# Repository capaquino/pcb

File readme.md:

Personal PCB projects portfolio

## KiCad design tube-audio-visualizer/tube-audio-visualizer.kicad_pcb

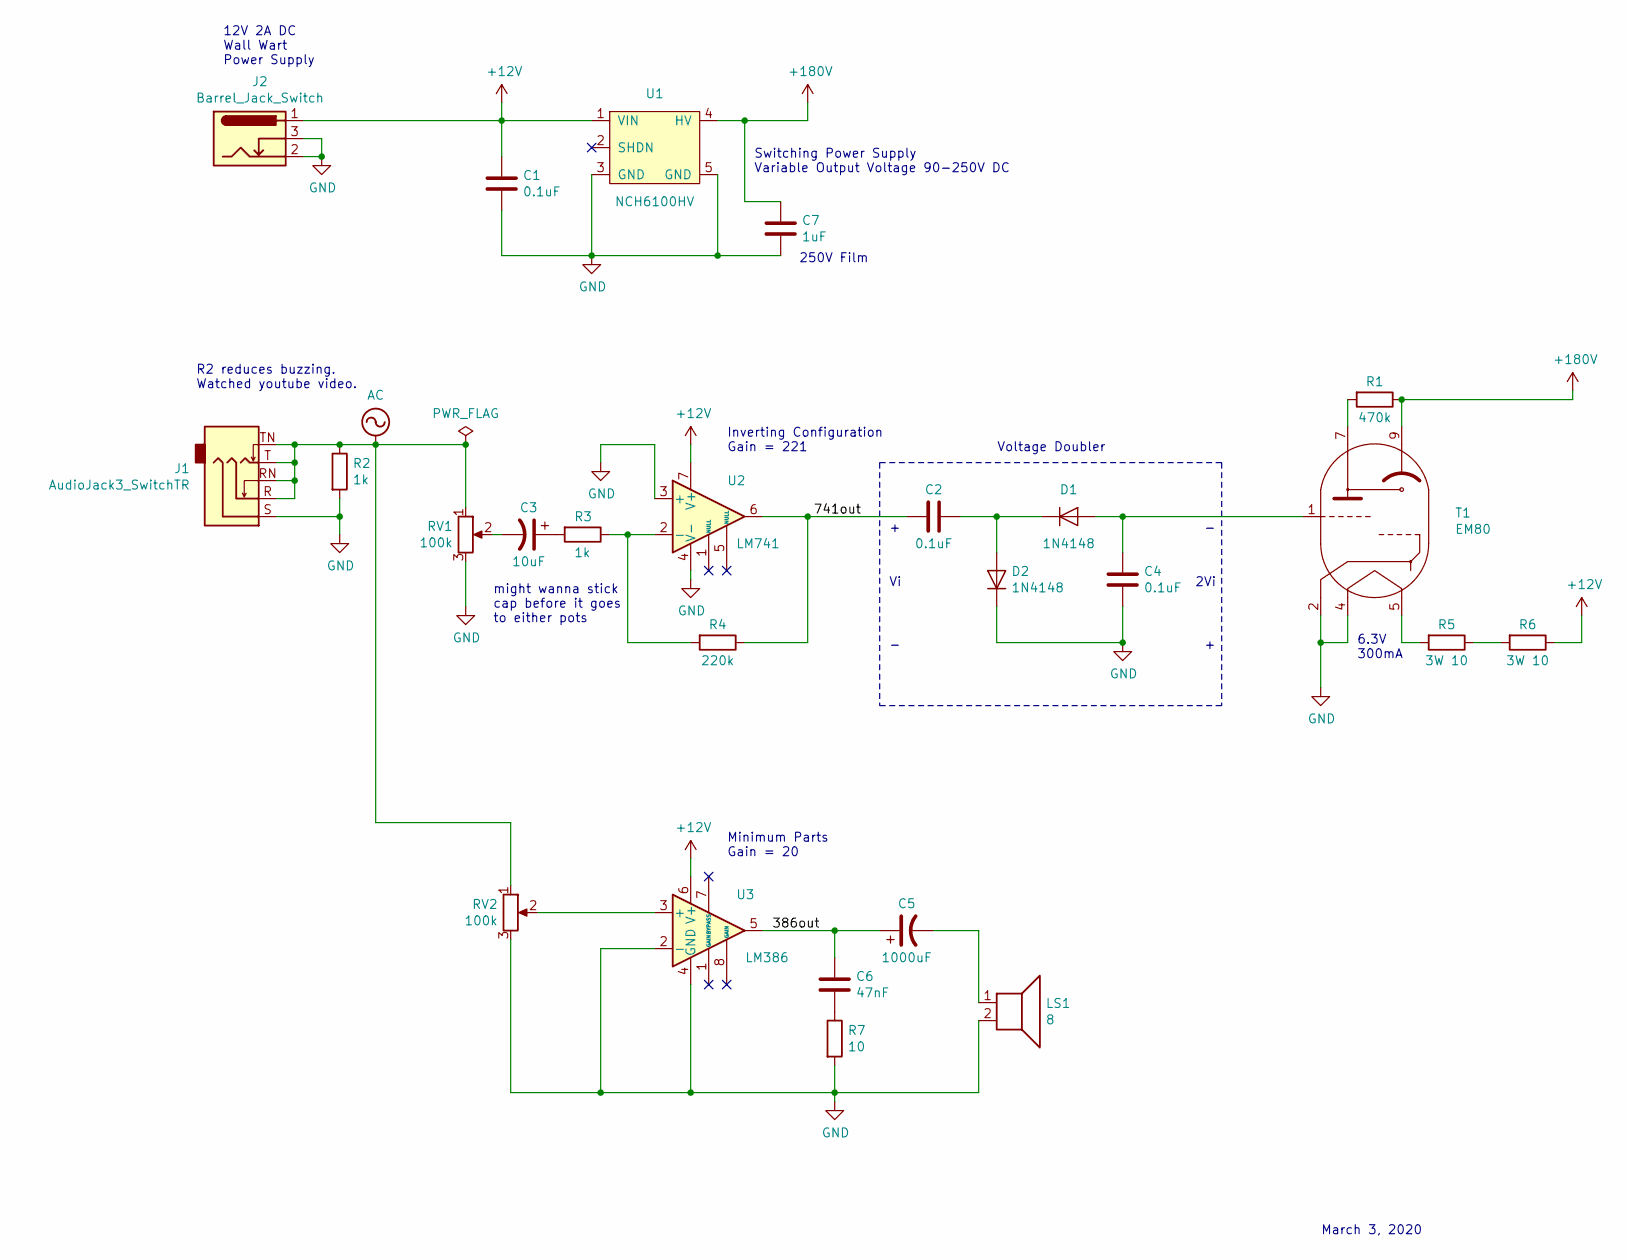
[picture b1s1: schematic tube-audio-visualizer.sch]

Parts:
C1, C2, C4: 0.1uF; C_Disc_D5.0mm_W2.5mm_P5.00mm
C3: 10uF; CP_Radial_D5.0mm_P2.00mm
C5: 1000uF; CP_Radial_D8.0mm_P3.50mm
C6: 47nF; C_Disc_D3.0mm_W2.0mm_P2.50mm
C7: 1uF; Cap_Film_250V_1uF_Nichicon
D1, D2: 1N4148; D_DO-35_SOD27_P7.62mm_Horizontal
J1: AudioJack3_SwitchTR; AudioJack_3_5_mm_Female
J2: Barrel_Jack_Switch; BarrelJack_CUI_PJ-102AH_Horizontal
LS1: 8; PinSocket_1x02_P2.54mm_Vertical
R1: 470k; R_Axial_DIN0207_L6.3mm_D2.5mm_P10.16mm_Horizontal
R2, R3: 1k; R_Axial_DIN0207_L6.3mm_D2.5mm_P10.16mm_Horizontal
R4: 220k; R_Axial_DIN0207_L6.3mm_D2.5mm_P10.16mm_Horizontal
R5, R6: 3W 10; R_Axial_DIN0516_L15.5mm_D5.0mm_P20.32mm_Horizontal
R7: 10; R_Axial_DIN0207_L6.3mm_D2.5mm_P10.16mm_Horizontal
RV1, RV2: 100k; Potentiometer_Bourns_3386P_Vertical
T1: EM80; Noval_B9A_Ceramic
U1: NCH6100HV; NCH6100HV_PinSockets
U2: LM741; DIP-8_W7.62mm
U3: LM386; DIP-8_W7.62mm

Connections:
+12V: C1.1, J2.1, R6.1, U1.1 (VIN), U2.7 (V+), U3.6 (V+)
+180V: C7.1, R1.1, T1.9 (display), U1.4 (HV)
/386out: C5.1, C6.1, U3.5
/741out: C2.2, R4.1, U2.6
AC: J1.R, J1.RN, J1.T, J1.TN, R2.1, RV1.1, RV2.1
GND: C1.2, C4.2, C7.2, D2.1 (K), J1.S, J2.2, J2.3, LS1.2, R2.2, R7.2, RV1.3, RV2.3, T1.2 (cathode), T1.4 (f1), U1.3 (GND), U1.5 (GND), U2.3 (+), U2.4 (V-), U3.2 (-), U3.4 (GND)
unnamed: C2.1, D1.1 (K), D2.2 (A)
unnamed: C3.1, R3.2
unnamed: C3.2, RV1.2
unnamed: C4.1, D1.2 (A), T1.1 (grid)
unnamed: C5.2, LS1.1
unnamed: C6.2, R7.1
unnamed: R1.2, T1.7 (plate)
unnamed: R3.1, R4.2, U2.2 (-)
unnamed: R5.1, R6.2
unnamed: R5.2, T1.5 (f2)
unnamed: RV2.2, U3.3 (+)

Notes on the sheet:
Voltage Doubler
2Vi
March 3, 2020
6.3V 300mA
Minimum Parts Gain = 20
Inverting Configuration Gain = 221
Switching Power Supply Variable Output Voltage 90-250V DC
might wanna stick cap before it goes to either pots
12V 2A DC Wall Wart Power Supply
R2 reduces buzzing. Watched youtube video.
250V Film

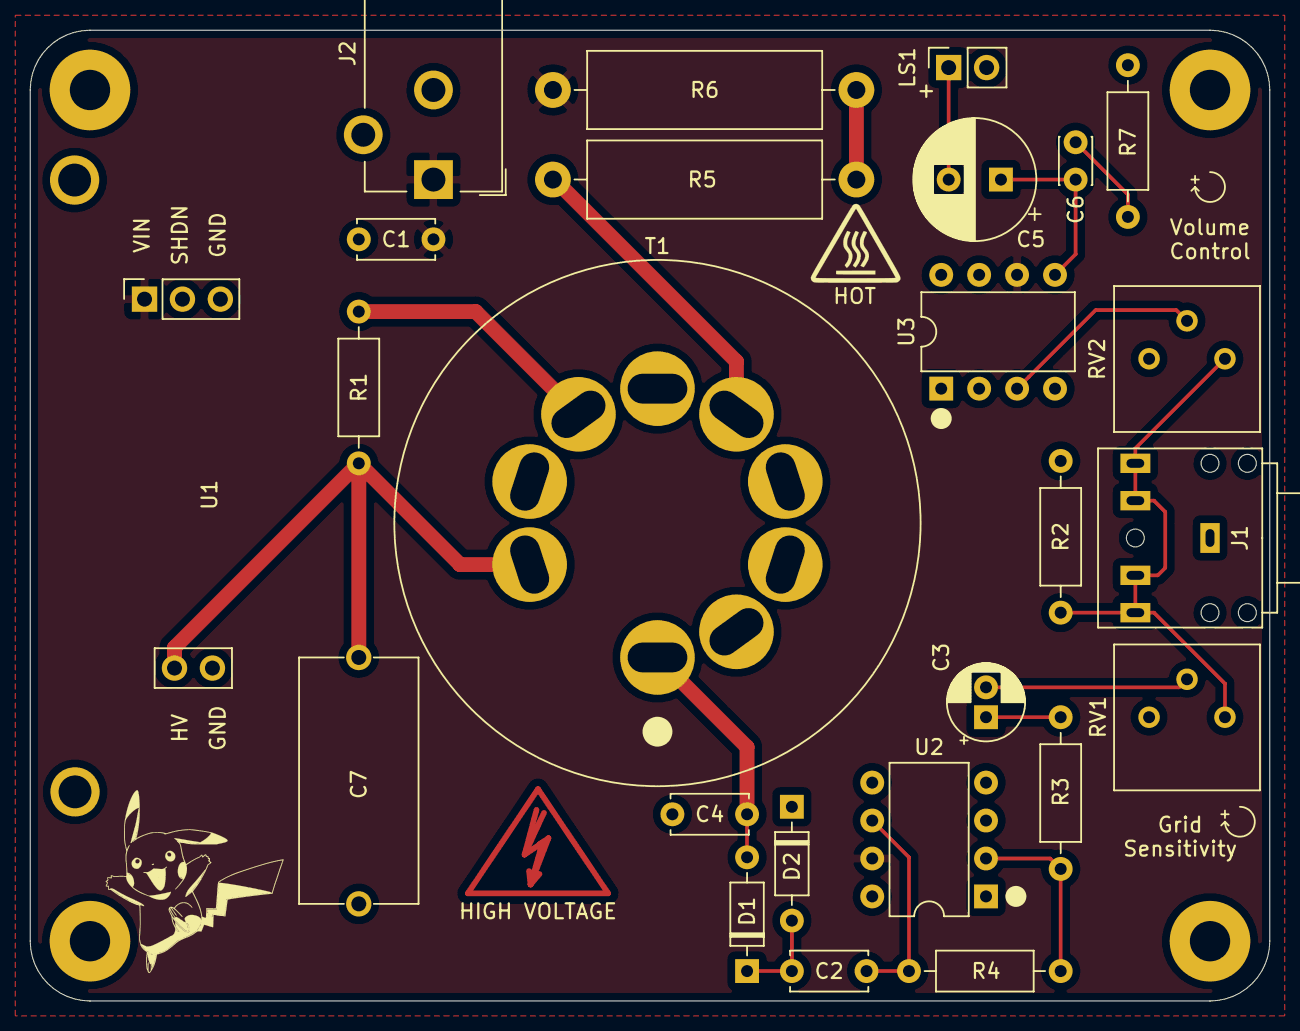
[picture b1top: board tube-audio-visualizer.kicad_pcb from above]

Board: 2 copper layers, 83.0 x 65.0 mm, 25 parts (0 on the bottom side), 17 nets.

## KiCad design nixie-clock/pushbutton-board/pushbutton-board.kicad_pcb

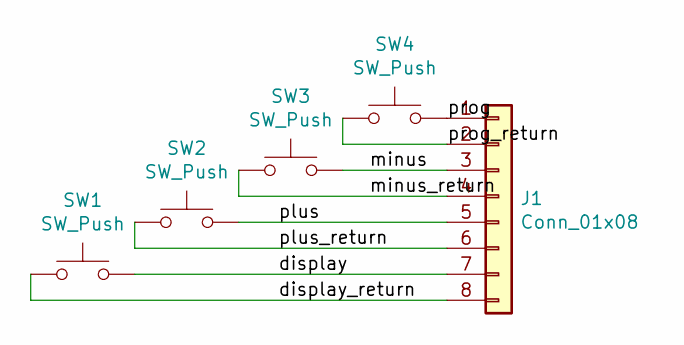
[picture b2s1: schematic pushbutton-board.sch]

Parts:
J1: Conn_01x08; PinHeader_2x04_P2.54mm_Vertical
SW1, SW2, SW3, SW4: SW_Push; SW_PUSH_6mm

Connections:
/display: J1.7, SW1.2
/display_return: J1.8, SW1.1
/minus: J1.3, SW3.2
/minus_return: J1.4, SW3.1
/plus: J1.5, SW2.2
/plus_return: J1.6, SW2.1
/prog: J1.1, SW4.2
/prog_return: J1.2, SW4.1

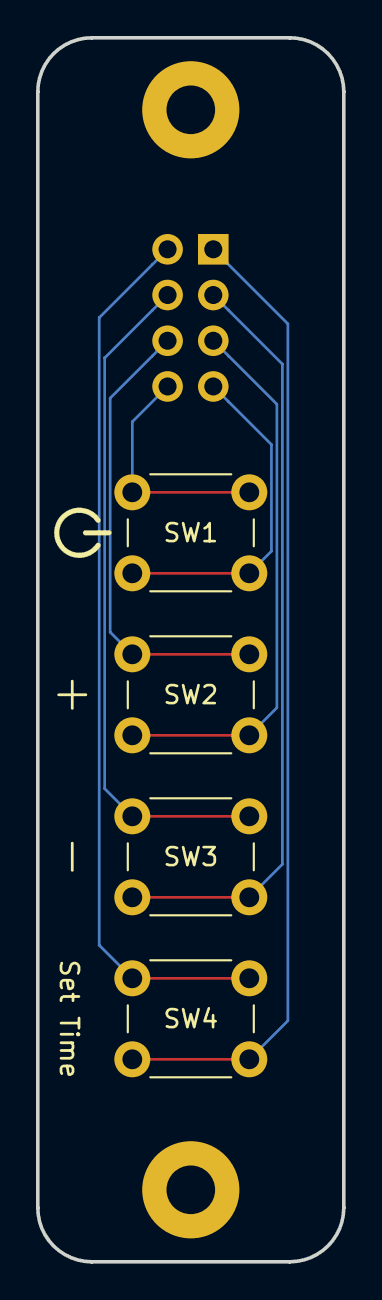
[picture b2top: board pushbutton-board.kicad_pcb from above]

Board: 2 copper layers, 17.0 x 68.0 mm, 5 parts (1 on the bottom side), 8 nets.

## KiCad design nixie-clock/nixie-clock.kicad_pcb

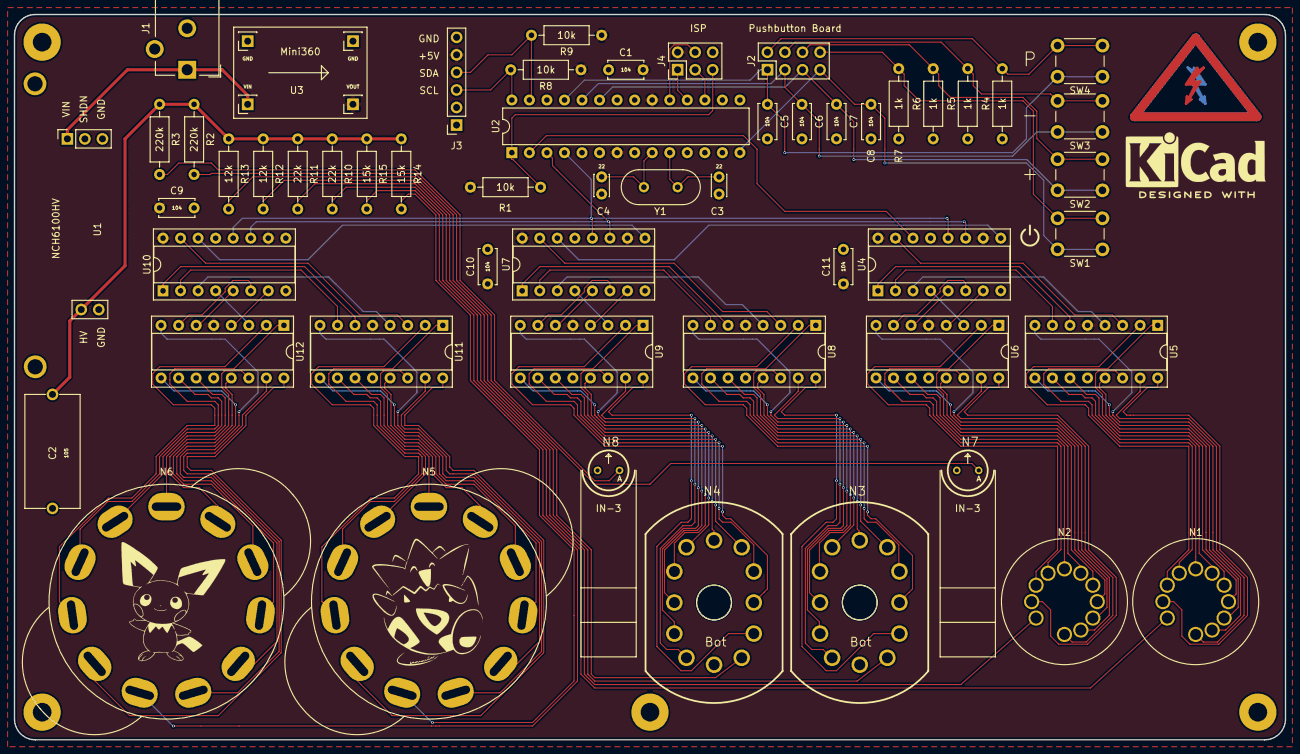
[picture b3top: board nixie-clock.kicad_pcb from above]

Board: 2 copper layers, 184.0 x 105.0 mm, 55 parts (0 on the bottom side), 117 nets.

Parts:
C1, C5, C6, C7, C8, C9, C10, C11: 0.1uF; C_Disc_D5.0mm_W2.5mm_P5.00mm
C2: 1uF; Cap_Film_250V_1uF_Nichicon
C3, C4: 22pF; C_Disc_D3.0mm_W2.0mm_P2.50mm
J1: Barrel_Jack_Switch; BarrelJack_CUI_PJ-102AH_Horizontal
J2: Conn_01x08; PinHeader_2x04_P2.54mm_Vertical
J3: Conn_01x06; PinSocket_1x06_P2.54mm_Vertical
J4: AVR-ISP-6; PinHeader_2x03_P2.54mm_Vertical
N1, N2: IN-2; IN-2_Socket_Pins
N3, N4: IN-12A; nixies-us-IN-12-DSUB
N5, N6: IN-1; IN-1_Socket
N7, N8: IN-3; IN-3_Bare
R1, R8, R9: 10k; R_Axial_DIN0207_L6.3mm_D2.5mm_P10.16mm_Horizontal
R2, R3: 220k; R_Axial_DIN0207_L6.3mm_D2.5mm_P10.16mm_Horizontal
R4, R5, R6, R7: 1k; R_Axial_DIN0207_L6.3mm_D2.5mm_P10.16mm_Horizontal
R10, R11: 22k; R_Axial_DIN0207_L6.3mm_D2.5mm_P10.16mm_Horizontal
R12, R13: 12k; R_Axial_DIN0207_L6.3mm_D2.5mm_P10.16mm_Horizontal
R14, R15: 15k; R_Axial_DIN0207_L6.3mm_D2.5mm_P10.16mm_Horizontal
SW1, SW2, SW3, SW4: SW_Push; SW_PUSH_6mm
U1: NCH6100HV; NCH6100HV_PinSockets
U2: ATmega328P-PU; DIP-28_W7.62mm
U3: Mini360_Buck; Mini360_PinSockets
U4, U7, U10: 74HC595; DIP-16_W7.62mm_Socket
U5, U6, U8, U9, U11, U12: 74141; DIP-16_W7.62mm_Socket
Y1: 8MHz; Crystal_HC49-4H_Vertical

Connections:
+5V: C1.1, C9.1, C10.1, C11.1, J3.5, J4.2, R1.1, R8.1, R9.1, U2.7, U2.20, U3.3, U4.10, U4.16, U5.5, U6.5, U7.10, U7.16, U8.5, U9.5, U10.10, U10.16, U11.5, U12.5
+12V: J1.1, U1.1, U3.1
+170V: C2.1, R2.1, R3.1, R10.1, R11.1, R12.1, R13.1, R14.1, R15.1, U1.4
/AnodeN7: N7.A, R2.2
/AnodeN8: N8.A, R3.2
/shiftout/AnodeN1: N1.A, R10.2
/shiftout/AnodeN2: N2.A, R11.2
/shiftout/AnodeN3: N3.A, R12.2
/shiftout/AnodeN4: N4.A, R13.2
/shiftout/AnodeN5: N5.A, R14.2
/shiftout/AnodeN6: N6.A, R15.2
/shiftout/N1_0: N1.0, U5.16
/shiftout/N1_1: N1.1, U5.15
/shiftout/N1_2: N1.2, U5.8
/shiftout/N1_3: N1.3, U5.9
/shiftout/N1_4: N1.4, U5.13
/shiftout/N1_5: N1.5, U5.14
/shiftout/N1_6: N1.6, U5.11
/shiftout/N1_7: N1.7, U5.10
/shiftout/N1_8: N1.8, U5.1
/shiftout/N1_9: N1.9, U5.2
/shiftout/N1_A: U4.15, U5.3
/shiftout/N1_B: U4.1, U5.6
/shiftout/N1_C: U4.2, U5.7
/shiftout/N1_D: U4.3, U5.4
/shiftout/N2_0: N2.0, U6.16
/shiftout/N2_1: N2.1, U6.15
/shiftout/N2_2: N2.2, U6.8
/shiftout/N2_3: N2.3, U6.9
/shiftout/N2_4: N2.4, U6.13
/shiftout/N2_5: N2.5, U6.14
/shiftout/N2_6: N2.6, U6.11
/shiftout/N2_7: N2.7, U6.10
/shiftout/N2_8: N2.8, U6.1
/shiftout/N2_9: N2.9, U6.2
/shiftout/N2_A: U4.4, U6.3
/shiftout/N2_B: U4.5, U6.6
/shiftout/N2_C: U4.6, U6.7
/shiftout/N2_D: U4.7, U6.4
/shiftout/N3_0: N3.0, U8.16
/shiftout/N3_1: N3.1, U8.15
/shiftout/N3_2: N3.2, U8.8
/shiftout/N3_3: N3.3, U8.9
/shiftout/N3_4: N3.4, U8.13
/shiftout/N3_5: N3.5, U8.14
/shiftout/N3_6: N3.6, U8.11
/shiftout/N3_7: N3.7, U8.10
/shiftout/N3_8: N3.8, U8.1
/shiftout/N3_9: N3.9, U8.2
/shiftout/N3_A: U7.15, U8.3
/shiftout/N3_B: U7.1, U8.6
/shiftout/N3_C: U7.2, U8.7
/shiftout/N3_D: U7.3, U8.4
/shiftout/N4_0: N4.0, U9.16
/shiftout/N4_1: N4.1, U9.15
/shiftout/N4_2: N4.2, U9.8
/shiftout/N4_3: N4.3, U9.9
/shiftout/N4_4: N4.4, U9.13
/shiftout/N4_5: N4.5, U9.14
/shiftout/N4_6: N4.6, U9.11
/shiftout/N4_7: N4.7, U9.10
/shiftout/N4_8: N4.8, U9.1
/shiftout/N4_9: N4.9, U9.2
/shiftout/N4_A: U7.4, U9.3
/shiftout/N4_B: U7.5, U9.6
/shiftout/N4_C: U7.6, U9.7
/shiftout/N4_D: U7.7, U9.4
/shiftout/N5_0: N5.0, U11.16
/shiftout/N5_1: N5.1, U11.15
/shiftout/N5_2: N5.2, U11.8
/shiftout/N5_3: N5.3, U11.9
/shiftout/N5_4: N5.4, U11.13
/shiftout/N5_5: N5.5, U11.14
/shiftout/N5_6: N5.6, U11.11
/shiftout/N5_7: N5.7, U11.10
/shiftout/N5_8: N5.8, U11.1
/shiftout/N5_9: N5.9, U11.2
/shiftout/N5_A: U10.15, U11.3
/shiftout/N5_B: U10.1, U11.6
/shiftout/N5_C: U10.2, U11.7
/shiftout/N5_D: U10.3, U11.4
/shiftout/N6_0: N6.0, U12.16
/shiftout/N6_1: N6.1, U12.15
/shiftout/N6_2: N6.2, U12.8
/shiftout/N6_3: N6.3, U12.9
/shiftout/N6_4: N6.4, U12.13
/shiftout/N6_5: N6.5, U12.14
/shiftout/N6_6: N6.6, U12.11
/shiftout/N6_7: N6.7, U12.10
/shiftout/N6_8: N6.8, U12.1
/shiftout/N6_9: N6.9, U12.2
/shiftout/N6_A: U10.4, U12.3
/shiftout/N6_B: U10.5, U12.6
/shiftout/N6_C: U10.6, U12.7
/shiftout/N6_D: U10.7, U12.4
GND: C1.2, C2.2, C3.2, C4.2, C5.2, C6.2, C7.2, C8.2, C9.2, C10.2, C11.2, J1.2, J1.3, J3.6, J4.6, N7.K, N8.K, R4.1, R5.1, R6.1, R7.1, U1.3, U1.5, U2.8, U2.22, U3.2, U3.4, U4.8, U4.13, U5.12, U6.12, U7.8, U7.13, U8.12, U9.12, U10.8, U10.13, U11.12, U12.12
unnamed: J2.2, R4.2, SW4.2
unnamed: J2.4, R5.2, SW3.2
unnamed: J2.6, R6.2, SW2.2
unnamed: J2.8, R7.2, SW1.2
unnamed: U4.9, U7.14
unnamed: U7.9, U10.14
SCL: J3.3, R8.2, U2.28
SDA: J3.4, R9.2, U2.27
SPI_MISO: J4.1, U2.18
SPI_MOSI: J4.4, U2.19
SPI_RST: J4.5, R1.2, U2.1
SPI_SCK: J4.3, U2.17
SRCLK: U2.3, U4.11, U7.11, U10.11
SRDATA: U2.2, U4.14
SRLATCH: U2.4, U4.12, U7.12, U10.12
XTAL1: C3.1, U2.10, Y1.1
XTAL2: C4.1, U2.9, Y1.2
pb_display_on: C8.1, J2.7, SW1.1, U2.14
pb_minus: C6.1, J2.3, SW3.1, U2.24
pb_plus: C7.1, J2.5, SW2.1, U2.23
pb_programming_select: C5.1, J2.1, SW4.1, U2.25

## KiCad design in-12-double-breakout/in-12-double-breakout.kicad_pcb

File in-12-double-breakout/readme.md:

IN12 breakout board kicad project.

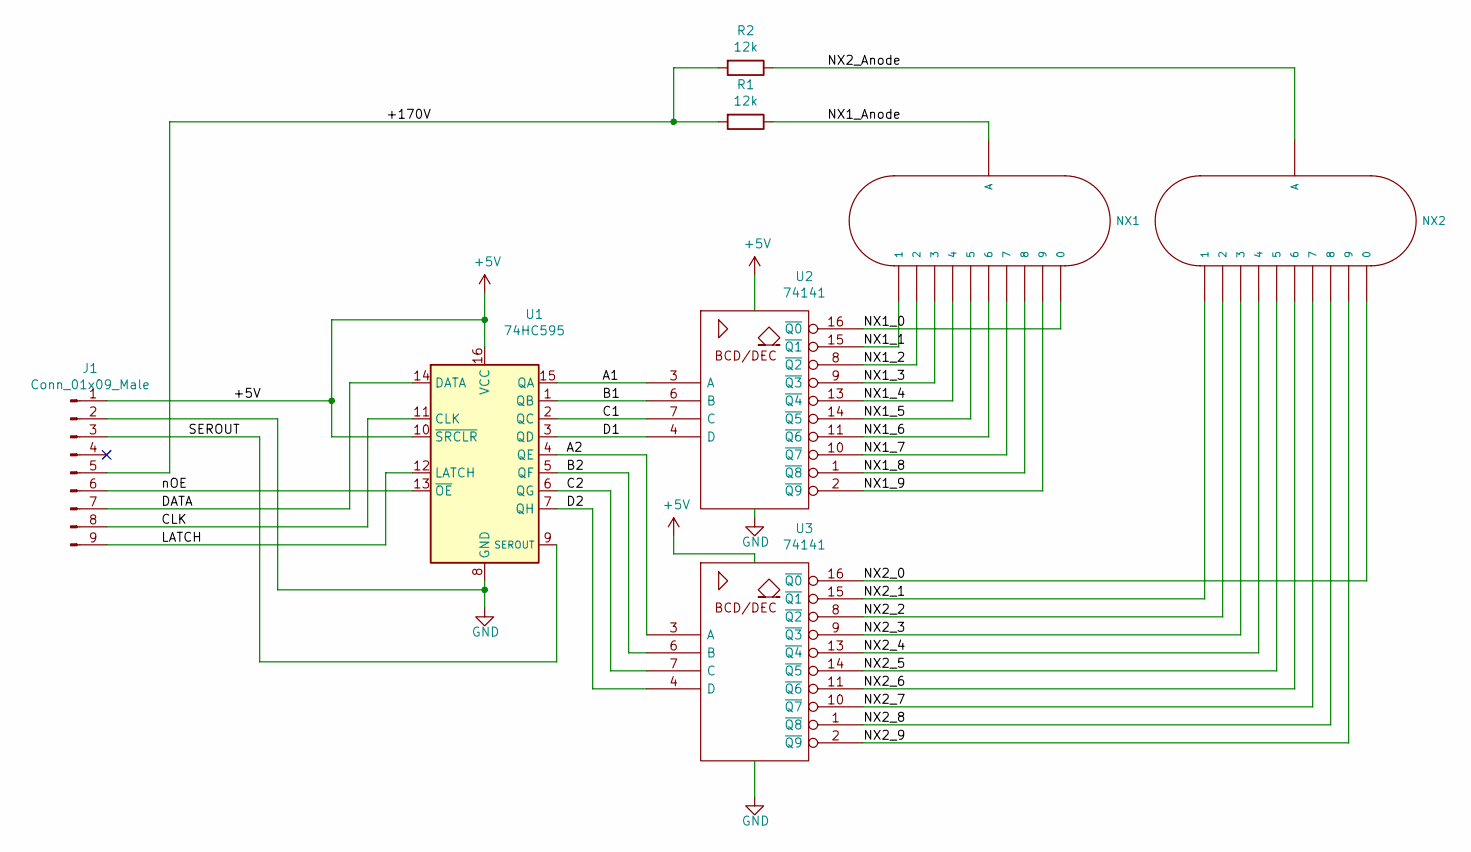
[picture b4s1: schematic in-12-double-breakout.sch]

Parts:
J1: Conn_01x09_Male; PinHeader_1x09_P2.54mm_Horizontal
NX1, NX2: IN-12A; nixies-us_IN-12
R1, R2: 12k; R_Axial_DIN0207_L6.3mm_D2.5mm_P10.16mm_Horizontal
U1: 74HC595; DIP-16_W7.62mm_Socket
U2, U3: 74141; DIP-16_W7.62mm_Socket

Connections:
+5V: J1.1, U1.10 (~SRCLR), U1.16 (VCC), U2.5 (VCC), U3.5 (VCC)
/+170V: J1.5, R1.2, R2.2
/A1: U1.15 (QA), U2.3 (A)
/A2: U1.4 (QE), U3.3 (A)
/B1: U1.1 (QB), U2.6 (B)
/B2: U1.5 (QF), U3.6 (B)
/C1: U1.2 (QC), U2.7 (C)
/C2: U1.6 (QG), U3.7 (C)
/CLK: J1.8, U1.11 (CLK)
/D1: U1.3 (QD), U2.4 (D)
/D2: U1.7 (QH), U3.4 (D)
/DATA: J1.7, U1.14 (DATA)
/LATCH: J1.9, U1.12 (LATCH)
/NX1_0: NX1.0, U2.16 (~Q0)
/NX1_1: NX1.1, U2.15 (~Q1)
/NX1_2: NX1.2, U2.8 (~Q2)
/NX1_3: NX1.3, U2.9 (~Q3)
/NX1_4: NX1.4, U2.13 (~Q4)
/NX1_5: NX1.5, U2.14 (~Q5)
/NX1_6: NX1.6, U2.11 (~Q6)
/NX1_7: NX1.7, U2.10 (~Q7)
/NX1_8: NX1.8, U2.1 (~Q8)
/NX1_9: NX1.9, U2.2 (~Q9)
/NX1_Anode: NX1.A, R1.1
/NX2_0: NX2.0, U3.16 (~Q0)
/NX2_1: NX2.1, U3.15 (~Q1)
/NX2_2: NX2.2, U3.8 (~Q2)
/NX2_3: NX2.3, U3.9 (~Q3)
/NX2_4: NX2.4, U3.13 (~Q4)
/NX2_5: NX2.5, U3.14 (~Q5)
/NX2_6: NX2.6, U3.11 (~Q6)
/NX2_7: NX2.7, U3.10 (~Q7)
/NX2_8: NX2.8, U3.1 (~Q8)
/NX2_9: NX2.9, U3.2 (~Q9)
/NX2_Anode: NX2.A, R2.1
/SEROUT: J1.3, U1.9 (SEROUT)
/nOE: J1.6, U1.13 (~OE)
GND: J1.2, U1.8 (GND), U2.12 (GND), U3.12 (GND)

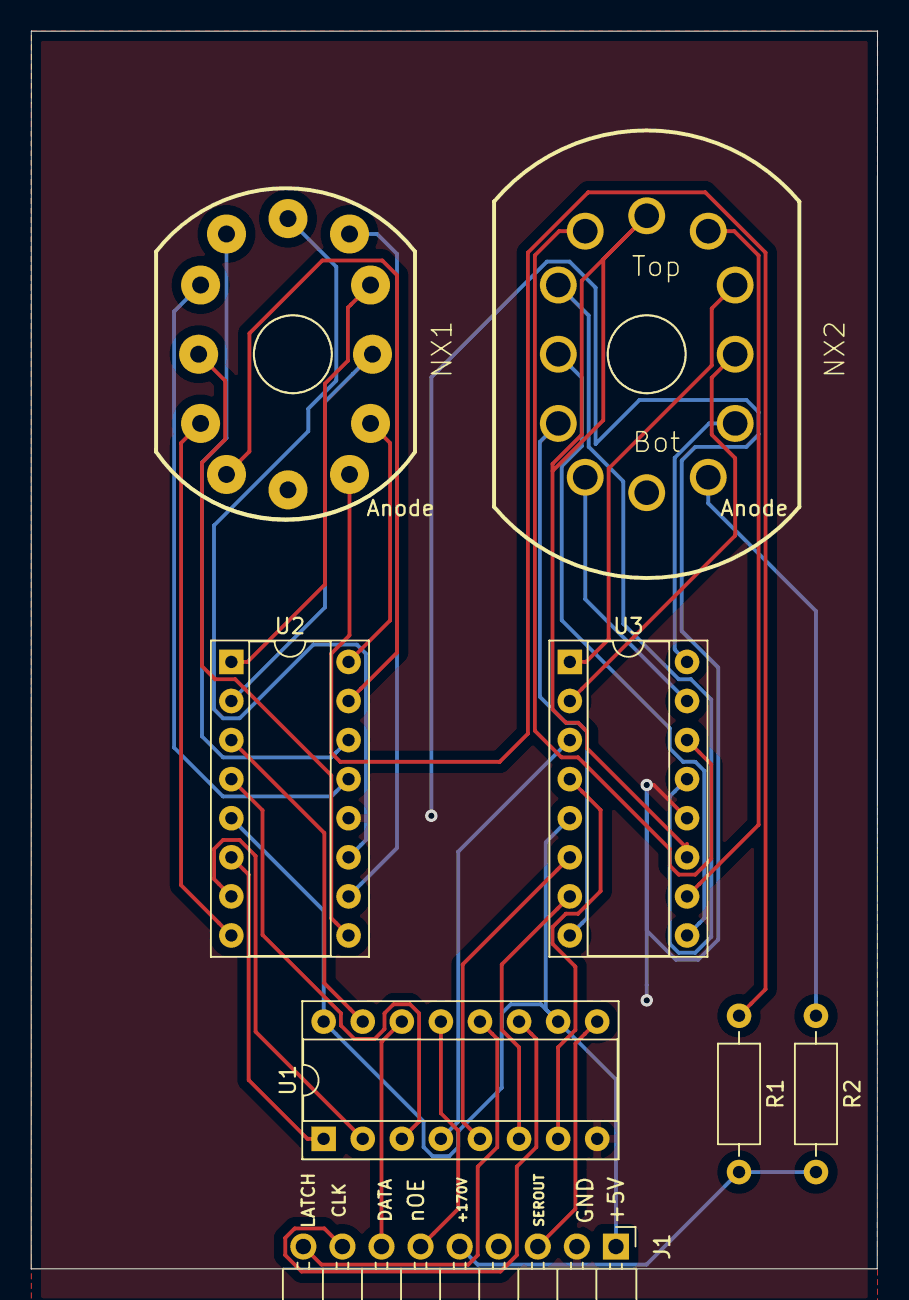
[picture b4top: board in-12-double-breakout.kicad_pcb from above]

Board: 2 copper layers, 55.0 x 80.5 mm, 8 parts (0 on the bottom side), 38 nets.

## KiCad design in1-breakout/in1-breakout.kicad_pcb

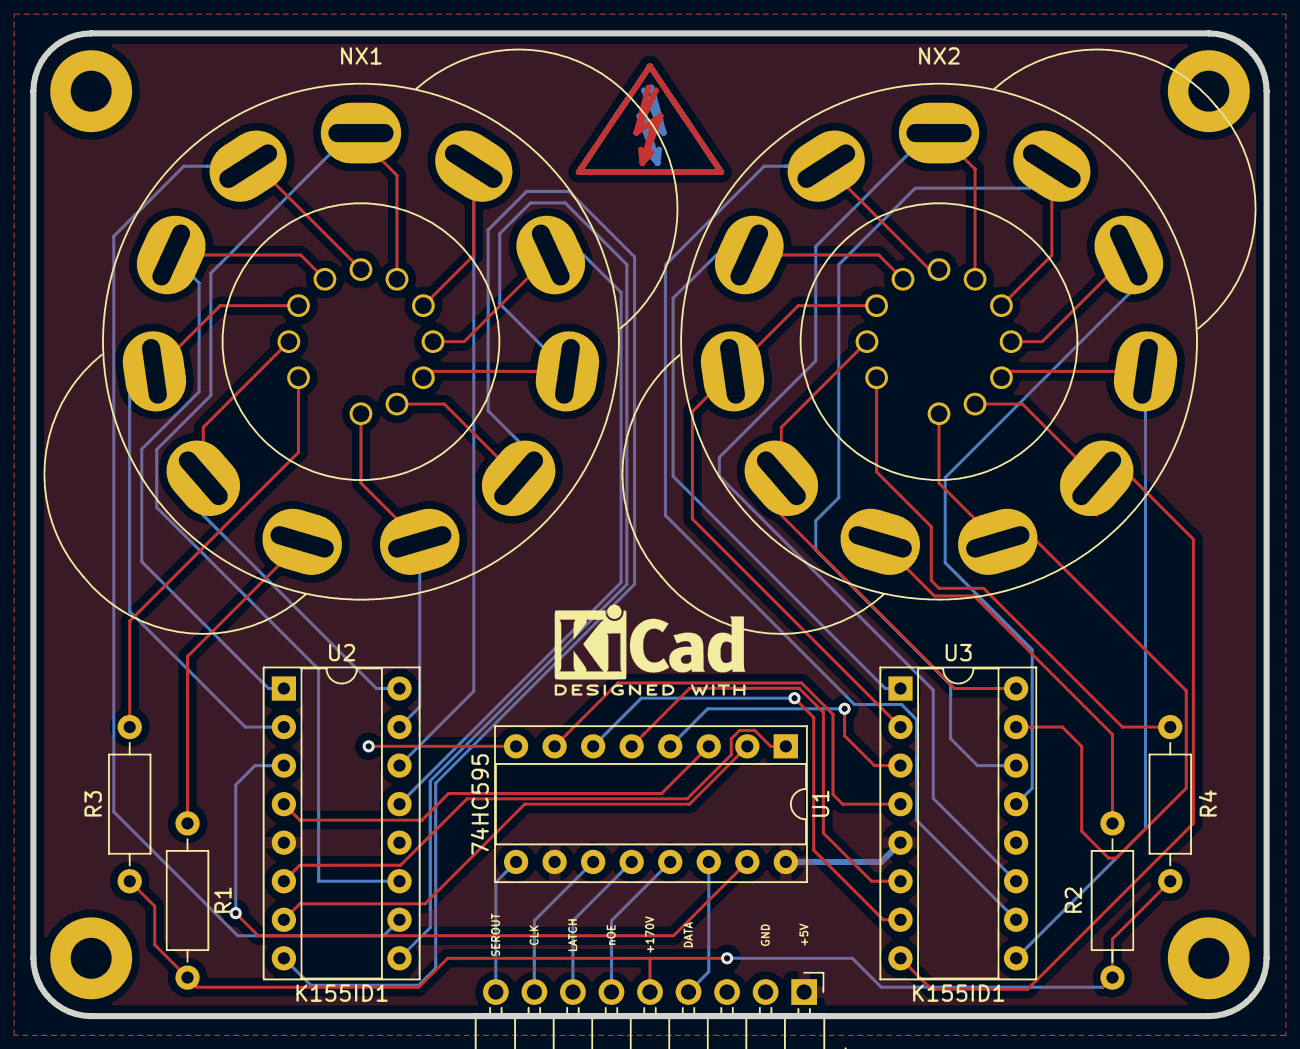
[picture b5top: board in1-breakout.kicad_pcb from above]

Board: 2 copper layers, 81.3 x 64.8 mm, 12 parts (0 on the bottom side), 40 nets.

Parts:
J1: Conn_01x09_Male; PinHeader_1x09_P2.54mm_Horizontal
NX1, NX2: IN-1; IN-1_Socket
NX3, NX4: IN-2; IN-2_Bare
R1, R2: 15k; R_Axial_DIN0207_L6.3mm_D2.5mm_P10.16mm_Horizontal
R3, R4: 22k; R_Axial_DIN0207_L6.3mm_D2.5mm_P10.16mm_Horizontal
U1: 74HC595; DIP-16_W7.62mm_Socket
U2, U3: K155ID1; DIP-16_W7.62mm_Socket

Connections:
+5V: J1.1, U1.10, U1.16, U2.5, U3.5
/+170V: J1.5, R1.2, R2.2, R3.1, R4.1
/A1: U1.15, U2.3
/A2: U1.4, U3.3
/B1: U1.1, U2.6
/B2: U1.5, U3.6
/C1: U1.2, U2.7
/C2: U1.6, U3.7
/CLK: J1.8, U1.11
/D1: U1.3, U2.4
/D2: U1.7, U3.4
/DATA: J1.4, U1.14
/LATCH: J1.7, U1.12
/NX1_0: NX1.0, NX3.0, U2.16
/NX1_1: NX1.1, NX3.1, U2.15
/NX1_2: NX1.2, NX3.2, U2.8
/NX1_3: NX1.3, NX3.3, U2.9
/NX1_4: NX1.4, NX3.4, U2.13
/NX1_5: NX1.5, NX3.5, U2.14
/NX1_6: NX1.6, NX3.6, U2.11
/NX1_7: NX1.7, NX3.7, U2.10
/NX1_8: NX1.8, NX3.8, U2.1
/NX1_9: NX1.9, NX3.9, U2.2
/NX1_Anode: NX1.A, R1.1
/NX2_0: NX2.0, NX4.0, U3.16
/NX2_1: NX2.1, NX4.1, U3.15
/NX2_2: NX2.2, NX4.2, U3.8
/NX2_3: NX2.3, NX4.3, U3.9
/NX2_4: NX2.4, NX4.4, U3.13
/NX2_5: NX2.5, NX4.5, U3.14
/NX2_6: NX2.6, NX4.6, U3.11
/NX2_7: NX2.7, NX4.7, U3.10
/NX2_8: NX2.8, NX4.8, U3.1
/NX2_9: NX2.9, NX4.9, U3.2
/NX2_Anode: NX2.A, R2.1
/NX3_Anode: NX3.A, R3.2
/NX4_Anode: NX4.A, R4.2
/SEROUT: J1.9, U1.9
/nOE: J1.6, U1.13
GND: J1.2, U1.8, U2.12, U3.12

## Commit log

2020-03-03 Initial commit. Has in1/in2 combined breakout board.
2020-03-04 Migrated all previous pcb projects to this repository.
2020-03-30 Added IN-2 footprint for socket pins.
2020-03-31 Added IN-2_Socket_Pins_test project for testing IN-2 footprint that uses eBay socket pins.
2020-03-31 Added nixie-clock project. Added symbols to schematic.
2020-04-06 Worked on schematic. Added child sheet. See TODO at left of root. Created Mini360 symbol.
2020-04-19 Added footprint for NCH6100HV switching power supply.
2020-04-22 Added footprints for mini360 buck and nichicon 1uf 250v film cap. Updated nixie-clock schematic with values. Starting to update schematic with daisy-chained configuration now that I figured out the p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
2020-04-23 Finished schematic for nixie clock main board. Added IN-3 footprint.
2020-04-23 Began nixie-clock pcb.
2020-04-23 Placed parts on board in approximate final locations. Created trace breakout for nixie tubes.
2020-04-24 Readded pushbuttons to mainboard as an option. Beginning K155ID1-nixie exchange zone.
2020-04-24 Both sides of exchange zone ready for connecting for IN-1, IN-2. Discovered IN-12 has reverse order so will need to redo traces for the K155ID1s attached to those nixies.
2020-04-24 Finished K155ID1-nixie exchange zone routing.
2020-04-24 Routed near microcontroller. Going to finish 74HC595-K155ID1 routing before returning to micro area.
2020-04-24 Finished seconds and minutes SR-K155ID1 exchange. Hours one is a bit different. Rotated SRs for better pin placement.
2020-04-24 About to begin inter-74HC595 signals. Save point.
2020-04-24 Finished inter-74HC595 routing.
2020-04-24 Fixed anode net names. Finished routing anode connections.
2020-04-24 Finished front silkscreen, added warning symbol, finished edge rounding and mounting holes. Need to add back silkscreen info and run DRC.
2020-04-24 Added back silkscreen. Ready for DRC.
2020-04-24 Ran DRC. Via holes in main exchange area too close by about 0.04mm. Save point.
2020-04-24 Add some extra silkscreen stuff.
2020-04-24 Added several image footprints. Added to nixie-clock silkscreen.
2020-04-24 Added res/cap values to silkscreen and more adjustments. Added footprint-tester board sent to OSHPARK.
2020-04-24 nixie-clock ready for fab assuming all footprints on footprints tester board checks out.
2020-04-25 Added silkscreen symbols for onbard pushbuttons. Created on/off power symbol.
2020-04-25 Finished pushbutton board. Minor silkscreen updates in nixie-clock. Ready for fabrication.
2020-05-03 Added barrel jack to schematic. Connected 3.5mm female connector. Created footprint for 3.5mm female connector. Added footprints to all schematic symbols.
2020-05-07 Version sent to OSHPARK. No changes. Refill and rerun DRC.
2020-09-12 Changed 3.5mm audio jack footprint pins from 12345 to S/R/RN/T/TN
2020-09-12 Initial schematic to pcb update and parts grouped.
2020-09-12 Parts and tracks laid. Adding text and extra silkscreen layer before sending off.
2020-09-12 Tube audio visualizer ready to be sent to fab. Added hot surface warning symbol footprint.
2020-09-15 ISP ports CLK & MOSI were wrong. Added blurb to note that its wrong. Didnt change it to reflect what the board actually has since I'm not going to make another rev.
2020-09-15 Added isp-correction-board for nixie-clock. Sent to fab.
